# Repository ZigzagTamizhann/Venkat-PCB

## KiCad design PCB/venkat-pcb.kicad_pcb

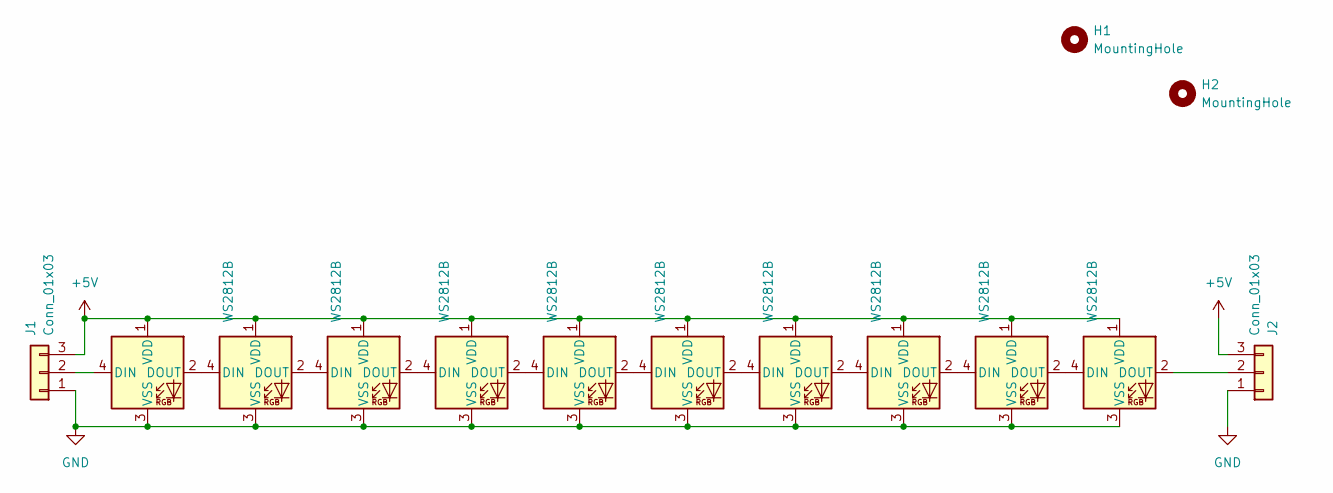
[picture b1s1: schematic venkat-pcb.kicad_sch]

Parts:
D1, D2, D3, D4, D5, D6, D7, D8, D9, D10: WS2812B; LED_WS2812B_PLCC4_5.0x5.0mm_P3.2mm
H1, H2: MountingHole; MountingHole_3.2mm_M3
J1, J2: Conn_01x03; PinHeader_1x03_P2.54mm_Vertical

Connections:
+5V: D1.1 (VDD), D2.1 (VDD), D3.1 (VDD), D4.1 (VDD), D5.1 (VDD), D6.1 (VDD), D7.1 (VDD), D8.1 (VDD), D9.1 (VDD), D10.1 (VDD), J1.3, J2.3
GND: D1.3 (VSS), D2.3 (VSS), D3.3 (VSS), D4.3 (VSS), D5.3 (VSS), D6.3 (VSS), D7.3 (VSS), D8.3 (VSS), D9.3 (VSS), D10.3 (VSS), J1.1, J2.1
unnamed: D1.4 (DIN), J1.2
unnamed: D1.2 (DOUT), D2.4 (DIN)
unnamed: D2.2 (DOUT), D3.4 (DIN)
unnamed: D3.2 (DOUT), D4.4 (DIN)
unnamed: D4.2 (DOUT), D5.4 (DIN)
unnamed: D5.2 (DOUT), D6.4 (DIN)
unnamed: D6.2 (DOUT), D7.4 (DIN)
unnamed: D7.2 (DOUT), D8.4 (DIN)
unnamed: D8.2 (DOUT), D9.4 (DIN)
unnamed: D9.2 (DOUT), D10.4 (DIN)
unnamed: D10.2 (DOUT), J2.2

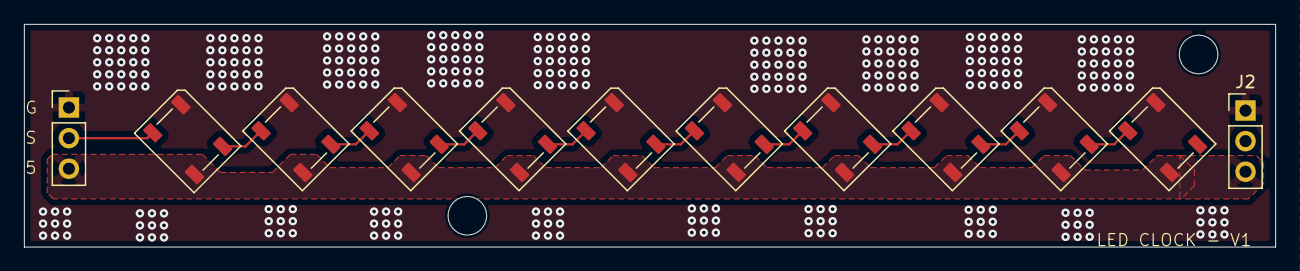
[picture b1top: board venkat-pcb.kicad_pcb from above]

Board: 2 copper layers, 103.9 x 18.5 mm, 14 parts (0 on the bottom side), 13 nets.

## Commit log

2025-12-31 CLOCK
